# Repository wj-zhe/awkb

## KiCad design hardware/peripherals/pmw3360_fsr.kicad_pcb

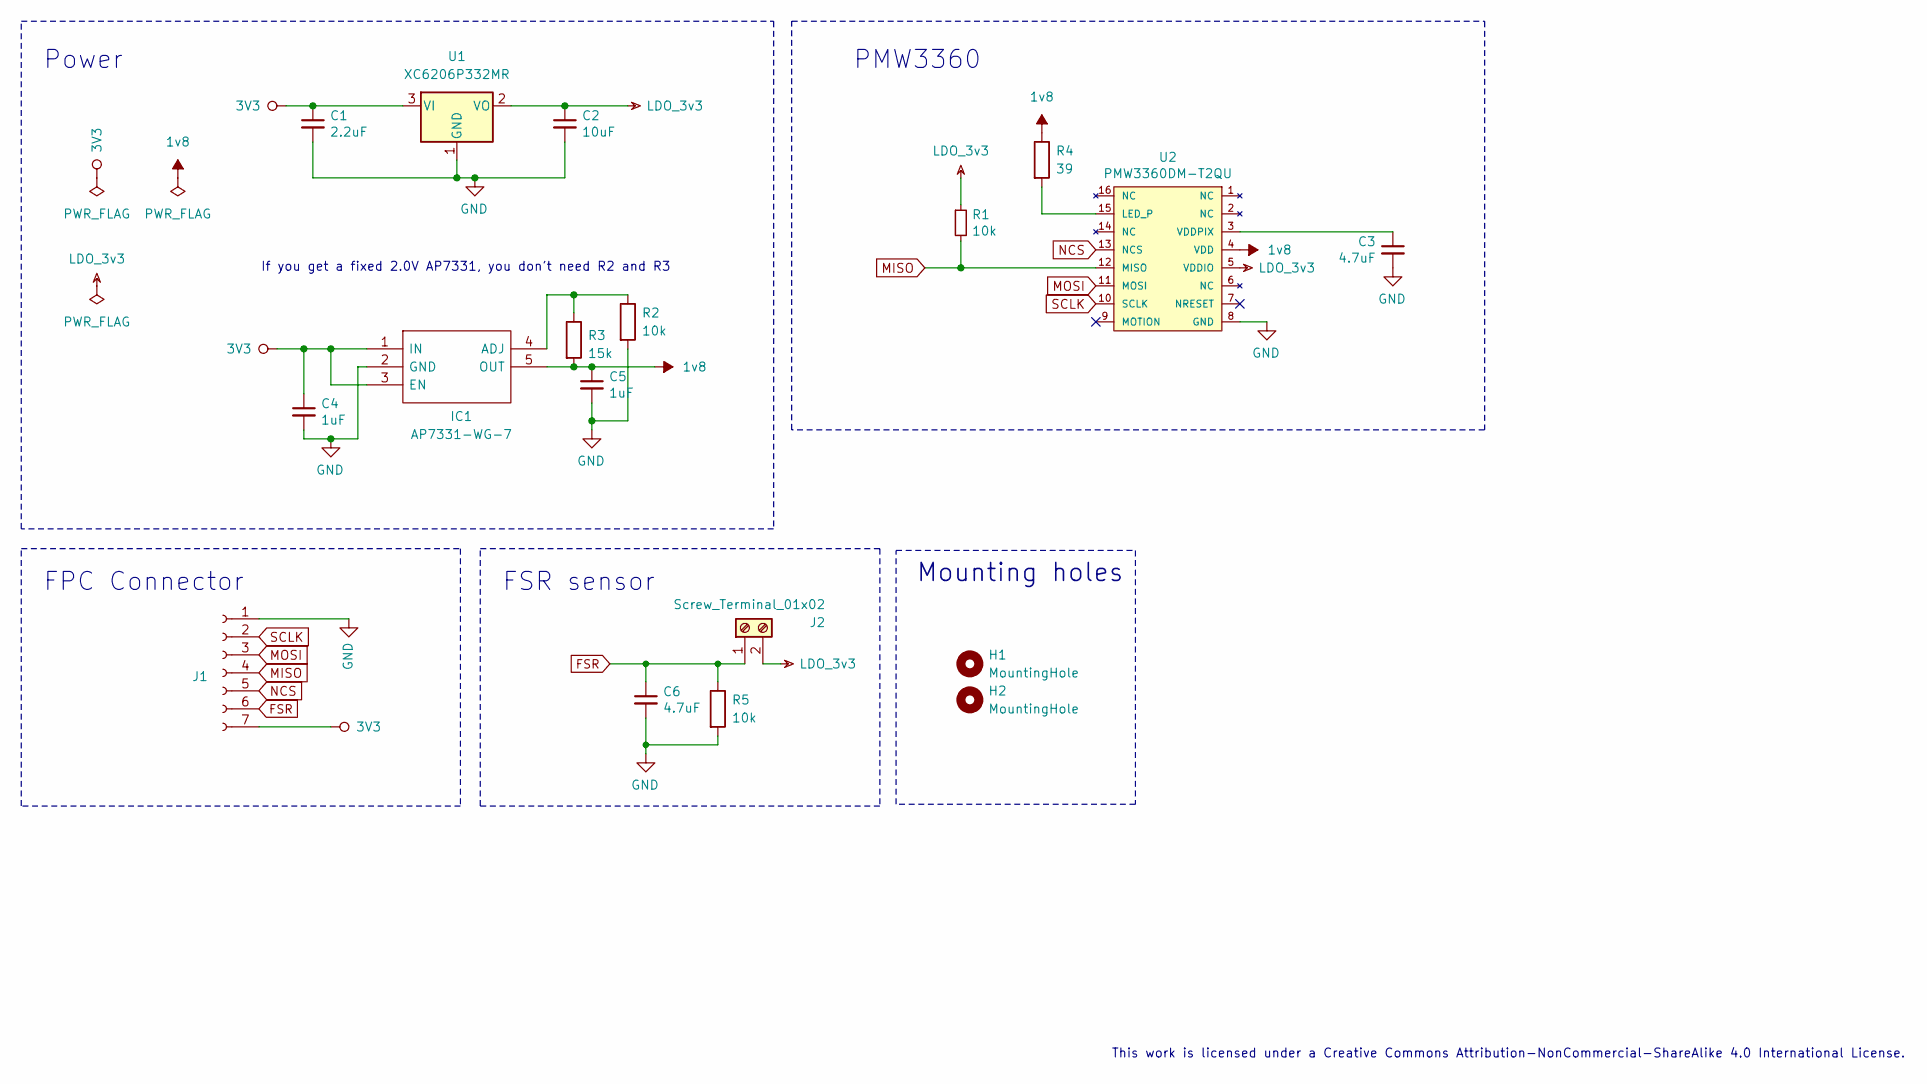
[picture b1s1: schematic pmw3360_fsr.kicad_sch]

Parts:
C1: 2.2uF; D_1206_3216Metric_Pad1.42x1.75mm_HandSolder; LCSC C1858
C2: 10uF; D_1206_3216Metric_Pad1.42x1.75mm_HandSolder; LCSC C152957
C3: 4.7uF; D_1206_3216Metric_Pad1.42x1.75mm_HandSolder; LCSC C29823
C4, C5: 1uF; D_1206_3216Metric_Pad1.42x1.75mm_HandSolder; LCSC C1926
C6: 4.7uF; D_1206_3216Metric_Pad1.42x1.75mm_HandSolder; LCSC C1858
H1, H2: MountingHole; MountingHole_3.2mm_M3
IC1: AP7331-WG-7; AP7331; Manufacturer_Part_Number AP7331-WG-7; Mouser Part Number 621-AP7331-WG-7
J1: Conn_01x07_Female; Conn_1x07-1MP_P0.5mm_Horizontal_Flip
J2: Screw_Terminal_01x02; TerminalBlock_Phoenix_MPT-0,5-2-2.54_1x02_P2.54mm_Horizontal
R1, R2, R5: 10k; D_1206_3216Metric_Pad1.42x1.75mm_HandSolder; LCSC C328409
R3: 15k; D_1206_3216Metric_Pad1.42x1.75mm_HandSolder; LCSC C351534
R4: 39; D_1206_3216Metric_Pad1.42x1.75mm_HandSolder; LCSC C153384
U1: XC6206P332MR; TSOT-23_HandSoldering; LCSC C347376
U2: PMW3360DM-T2QU; PMW3360DM_DIP-16_W10.16mm

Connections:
1v8: C5.1, IC1.5 (OUT), R3.2, R4.1, U2.4 (VDD)
3V3: C1.1, C4.1, IC1.1 (IN), IC1.3 (EN), J1.7, U1.3 (VI)
FSR: C6.1, J1.6, J2.1, R5.1
GND: C1.2, C2.2, C3.2, C4.2, C5.2, C6.2, IC1.2 (GND), J1.1, R2.2, R5.2, U1.1 (GND), U2.8 (GND)
LDO_3v3: C2.1, J2.2, R1.1, U1.2 (VO), U2.5 (VDDIO)
MISO: J1.4, R1.2, U2.12 (MISO)
MOSI: J1.3, U2.11 (MOSI)
NCS: J1.5, U2.13 (NCS)
unnamed: IC1.4 (ADJ), R2.1, R3.1
unnamed: R4.2, U2.15 (LED_P)
unnamed: C3.1, U2.3 (VDDPIX)
SCLK: J1.2, U2.10 (SCLK)

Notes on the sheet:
This work is licensed under a Creative Commons Attribution-NonCommercial-ShareAlike 4.0 International License.
Mounting holes
FSR sensor
If you get a fixed 2.0V AP7331, you don't need R2 and R3
Power
PMW3360
FPC Connector

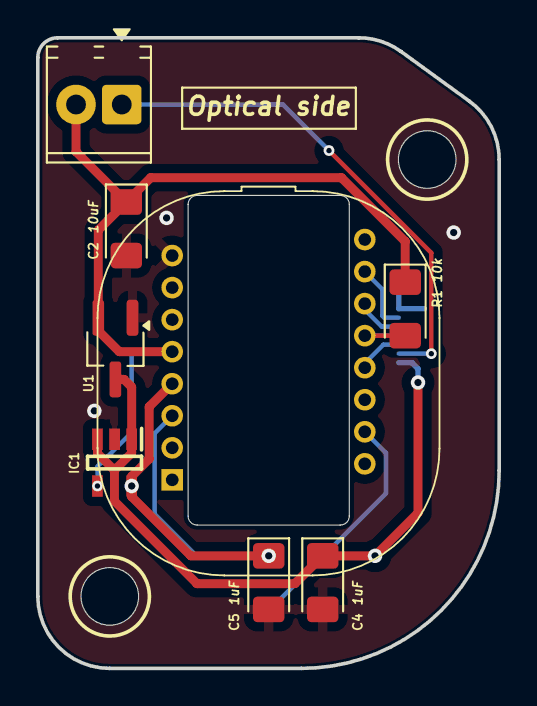
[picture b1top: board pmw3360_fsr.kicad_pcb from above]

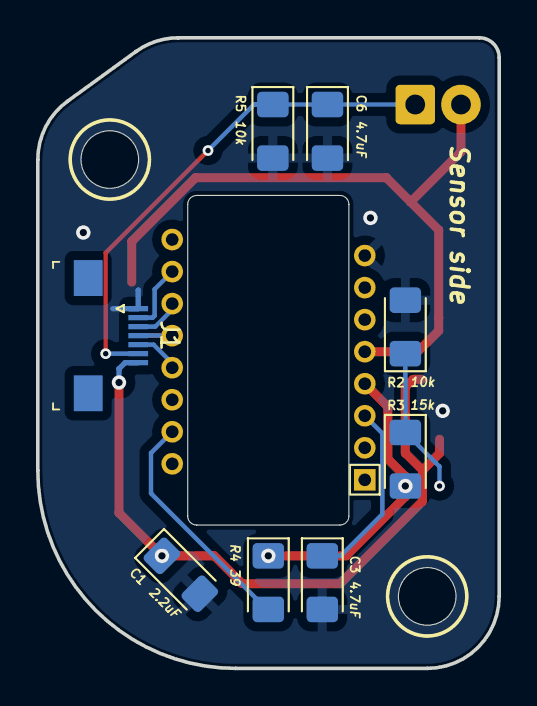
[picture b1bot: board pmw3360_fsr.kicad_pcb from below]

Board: 2 copper layers, 25.6 x 35.0 mm, 18 parts (9 on the bottom side), 12 nets.

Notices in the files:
hardware/peripherals/pmw3360_fsr/pmw3360_fsr.kicad_sch:
Copyright Quentin Lebastard
